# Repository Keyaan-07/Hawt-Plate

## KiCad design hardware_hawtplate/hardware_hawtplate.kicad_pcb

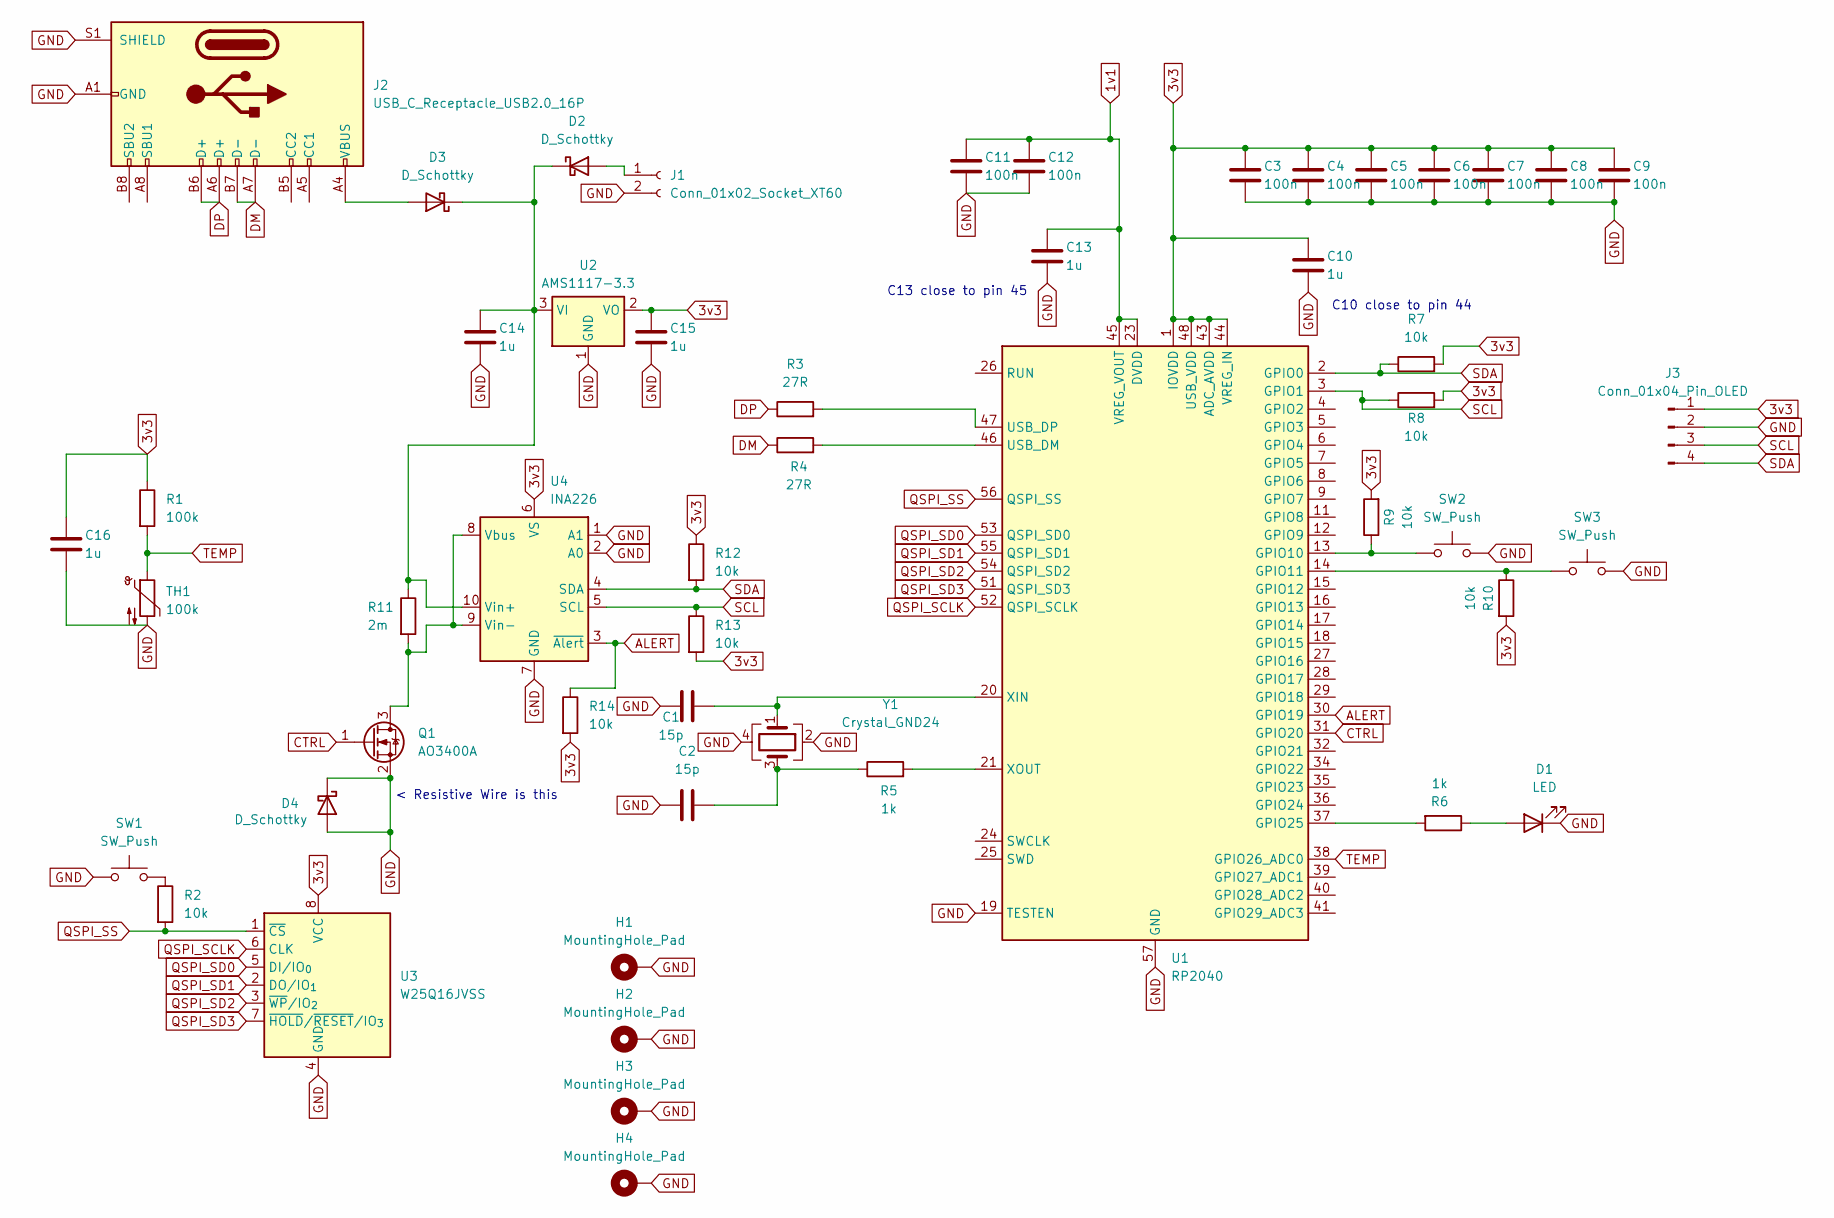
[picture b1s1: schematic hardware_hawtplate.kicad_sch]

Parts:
C1, C2: 15p; C_0402_1005Metric
C3, C4, C5, C6, C7, C8, C9, C11, C12: 100n; C_0402_1005Metric
C10, C13, C14, C15, C16: 1u; C_0402_1005Metric
D1: LED; LED_0402_1005Metric
D2: D_Schottky; D_SMC
D3, D4: D_Schottky; D_SMA
H1, H2, H3, H4: MountingHole_Pad; MountingHole_3.2mm_M3_Pad_Via
J1: Conn_01x02_Socket_XT60; PinHeader_1x02_P2.54mm_Vertical
J2: USB_C_Receptacle_USB2.0_16P; USB_C_Receptacle_XKB_U262-16XN-4BVC11
J3: Conn_01x04_Pin_OLED; PinHeader_1x04_P2.54mm_Vertical
Q1: AO3400A; SOT-23
R1: 100k; R_0402_1005Metric
R2, R7, R8, R9, R10, R12, R13, R14: 10k; R_0402_1005Metric
R3, R4: 27R; R_0402_1005Metric
R5, R6: 1k; R_0402_1005Metric
R11: 2m; R_0805_2012Metric
SW1, SW2, SW3: SW_Push; SW_SPST_PTS810
TH1: 100k; R_0402_1005Metric
U1: RP2040; QFN-56-1EP_7x7mm_P0.4mm_EP3.2x3.2mm
U2: AMS1117-3.3; SOT-89-3
U3: W25Q16JVSS; SOIC-8_5.3x5.3mm_P1.27mm
U4: INA226; VSSOP-10_3x3mm_P0.5mm
Y1: Crystal_GND24; Crystal_SMD_3225-4Pin_3.2x2.5mm

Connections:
1v1: C11.2, C12.2, C13.2, U1.23 (DVDD), U1.45 (VREG_VOUT), U1.50 (DVDD)
3v3: C3.2, C4.2, C5.2, C6.2, C7.2, C8.2, C9.2, C10.2, C15.2, C16.2, J3.1, R1.1, R7.2, R8.2, R9.2, R10.2, R12.1, R13.2, R14.2, U1.1 (IOVDD), U1.10 (IOVDD), U1.22 (IOVDD), U1.33 (IOVDD), U1.42 (IOVDD), U1.43 (ADC_AVDD), U1.44 (VREG_IN), U1.48 (USB_VDD), U1.49 (IOVDD), U2.2 (VO), U3.8 (VCC), U4.6 (VS)
ALERT: R14.1, U1.30 (GPIO19), U4.3 (~Alert)
CTRL: Q1.1 (G), U1.31 (GPIO20)
DM: J2.A7 (D-), J2.B7 (D-), R4.1
DP: J2.A6 (D+), J2.B6 (D+), R3.1
GND: C1.1, C2.1, C3.1, C4.1, C5.1, C6.1, C7.1, C8.1, C9.1, C10.1, C11.1, C12.1, C13.1, C14.1, C15.1, C16.1, D1.1 (K), D4.1 (K), D4.2 (A), H1.1, H2.1, H3.1, H4.1, J1.2, J2.A1 (GND), J2.A12 (GND), J2.B1 (GND), J2.B12 (GND), J2.S1 (SHIELD), J3.2, Q1.2 (S), SW1.1, SW2.2, SW3.2, TH1.2, U1.19 (TESTEN), U1.57 (GND), U2.1 (GND), U3.4 (GND), U4.1 (A1), U4.2 (A0), U4.7 (GND), Y1.2, Y1.4
unnamed: C2.2, R5.1, Y1.3
unnamed: D1.2 (A), R6.1
unnamed: D2.2 (A), J1.1
unnamed: C14.2, D2.1 (K), D3.1 (K), R11.1, U2.3 (VI), U4.10 (Vin+)
unnamed: D3.2 (A), J2.A4 (VBUS), J2.A9 (VBUS), J2.B4 (VBUS), J2.B9 (VBUS)
unnamed: Q1.3 (D), R11.2, U4.8 (Vbus), U4.9 (Vin-)
unnamed: R2.1, SW1.2
unnamed: R9.1, SW2.1, U1.13 (GPIO10)
unnamed: R10.1, SW3.1, U1.14 (GPIO11)
unnamed: R6.2, U1.37 (GPIO25)
unnamed: R4.2, U1.46 (USB_DM)
unnamed: R3.2, U1.47 (USB_DP)
unnamed: C1.2, U1.20 (XIN), Y1.1
unnamed: R5.2, U1.21 (XOUT)
QSPI_SCLK: U1.52 (QSPI_SCLK), U3.6 (CLK)
QSPI_SD0: U1.53 (QSPI_SD0), U3.5 (DI/IO_{0})
QSPI_SD1: U1.55 (QSPI_SD1), U3.2 (DO/IO_{1})
QSPI_SD2: U1.54 (QSPI_SD2), U3.3 (~WP/IO_{2})
QSPI_SD3: U1.51 (QSPI_SD3), U3.7 (~HOLD/~RESET/IO_{3})
QSPI_SS: R2.2, U1.56 (QSPI_SS), U3.1 (~CS)
SCL: J3.3, R8.1, R13.1, U1.3 (GPIO1), U4.5 (SCL)
SDA: J3.4, R7.1, R12.2, U1.2 (GPIO0), U4.4 (SDA)
TEMP: R1.2, TH1.1, U1.38 (GPIO26_ADC0)

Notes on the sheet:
C13 close to pin 45
C10 close to pin 44
< Resistive Wire is this

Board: 2 copper layers, 51 parts (0 on the bottom side), 30 nets, no tracks yet.

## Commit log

2025-06-03 New Mosfet
2025-06-03 Control circuitry and thermistor working
2025-06-03 Control circuitry and thermistor working and PID
2025-06-03 Many Changes
2025-06-03 Added Time spent
2025-06-03 Thoughts on PID and PCB Size
2025-06-05 Update Journal
2025-06-05 Schematic
2025-06-05 schematic and PCB
2025-06-05 Total Time Spent
2025-06-05 Not Working Today now
2025-06-05 Final Commit on June 5 I guess
